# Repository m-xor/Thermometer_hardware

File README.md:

# Thermometer_hardware

PCBs designed for ZS60 universal case https://www.tme.eu/pl/details/z60-abs/obudowy-z-panelem/kradex/z60-abs/
The device consists of three PCB:
- LCD display board

- main board

- receiver board

- The device

Firmware: https://github.com/m-xor/Thermometer_receiver

- Known issues
 * power socket is placed to deep
 * PA9, PA10 could be routed to solder pads in case of need accessing bootloader

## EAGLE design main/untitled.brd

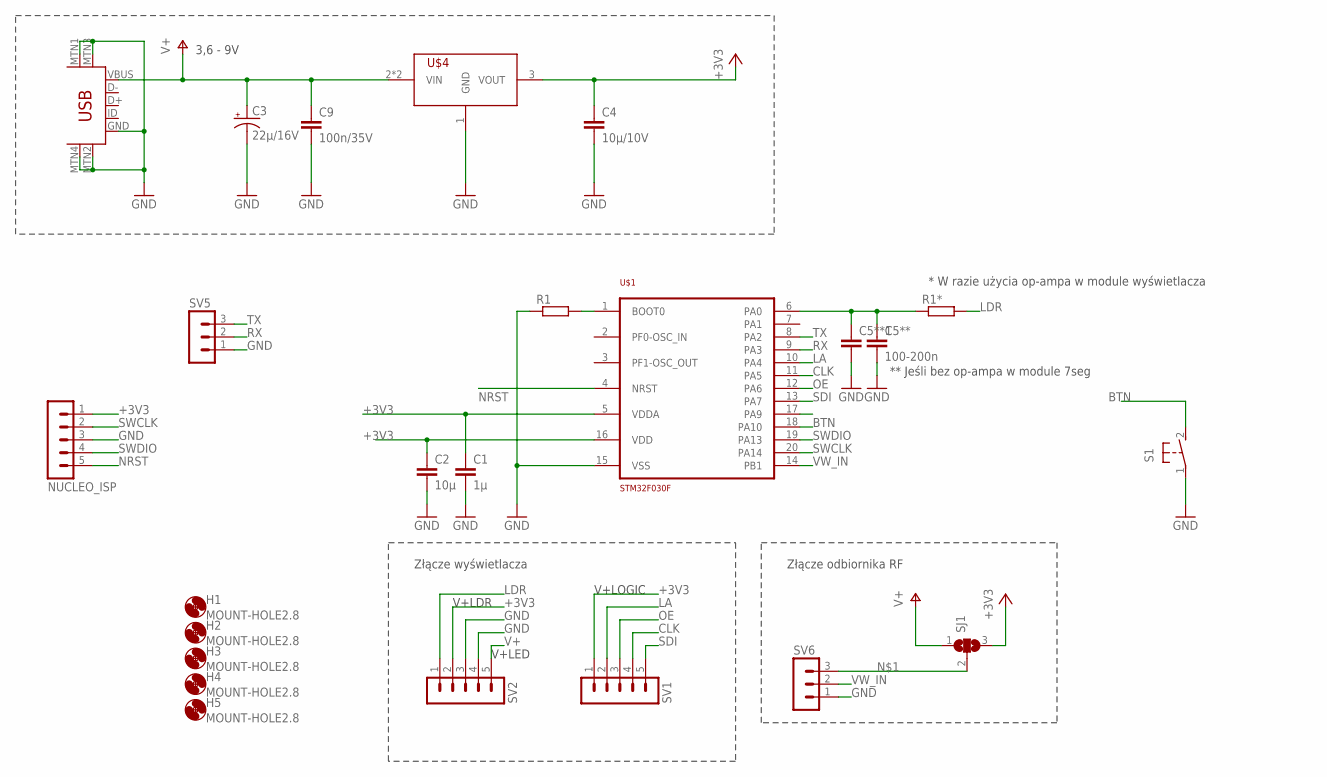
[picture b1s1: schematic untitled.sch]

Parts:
C1: 1µ; C0603
C2: 10µ; C0603
C3: 22µ/16V; E2,5-6
C4: 10µ/10V; C0603
C5**: 100-200n; C0603
C5**1: C-EUC0603; C0603
C9: 100n/35V; C0805
H1, H2, H3, H4, H5: MOUNT-HOLE2.8; 2,8
NUCLEO_ISP: MA05-1
R1, R1*: R-EU_R0603; R0603
S1: 31-XX; B3F-31XX
SJ1: SJ2W; SJ_2
SV1, SV2: MA05-1
SV5, SV6: MA03-1
U$1: STM32F030F; TSSOP20
U$2: USB-MINIB-5PIN; USB-MINIB
U$4: HT7333; SOT89

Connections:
+3V3: C1.1, C2.1, C4.1, NUCLEO_ISP.1, SJ1.3, SV1.1, SV2.2, U$1.5 (VDDA), U$1.16 (VDD), U$4.3 (VOUT)
BTN: S1.2 (S), U$1.18 (PA10)
CLK: SV1.4, U$1.11 (PA5)
GND: C1.2, C2.2, C3.-, C4.2, C5**.2, C5**1.2, C9.2, NUCLEO_ISP.3, R1.1, S1.1, SV2.3, SV2.4, SV5.1, SV6.1, U$1.15 (VSS), U$2.GND, U$2.MTN1 (MTN2), U$2.MTN2 (MTN3), U$2.MTN3 (MTN1), U$2.MTN4, U$4.1 (GND)
LA: SV1.2, U$1.10 (PA4)
LDR: R1*.2, SV2.1
unnamed: SJ1.2, SV6.3
unnamed: C5**.1, C5**1.1, R1*.1, U$1.6 (PA0)
unnamed: R1.2, U$1.1 (BOOT0)
NRST: NUCLEO_ISP.5, U$1.4 (NRST)
OE: SV1.3, U$1.12 (PA6)
RX: SV5.2, U$1.9 (PA3)
SDI: SV1.5, U$1.13 (PA7)
SWCLK: NUCLEO_ISP.2, U$1.20 (PA14)
SWDIO: NUCLEO_ISP.4, U$1.19 (PA13)
TX: SV5.3, U$1.8 (PA2)
V+: C3.+, C9.1, SJ1.1, SV2.5, U$2.VBUS, U$4.2 (VIN), U$4.2.1 (VIN)
VW_IN: SV6.2, U$1.14 (PB1)

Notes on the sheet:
* W razie użycia op-ampa w module wyświetlacza
** Jeśli bez op-ampa w module 7seg
3,6 - 9V
Złącze wyświetlacza
Złącze odbiornika RF
V+LDR
V+LED
V+LOGIC

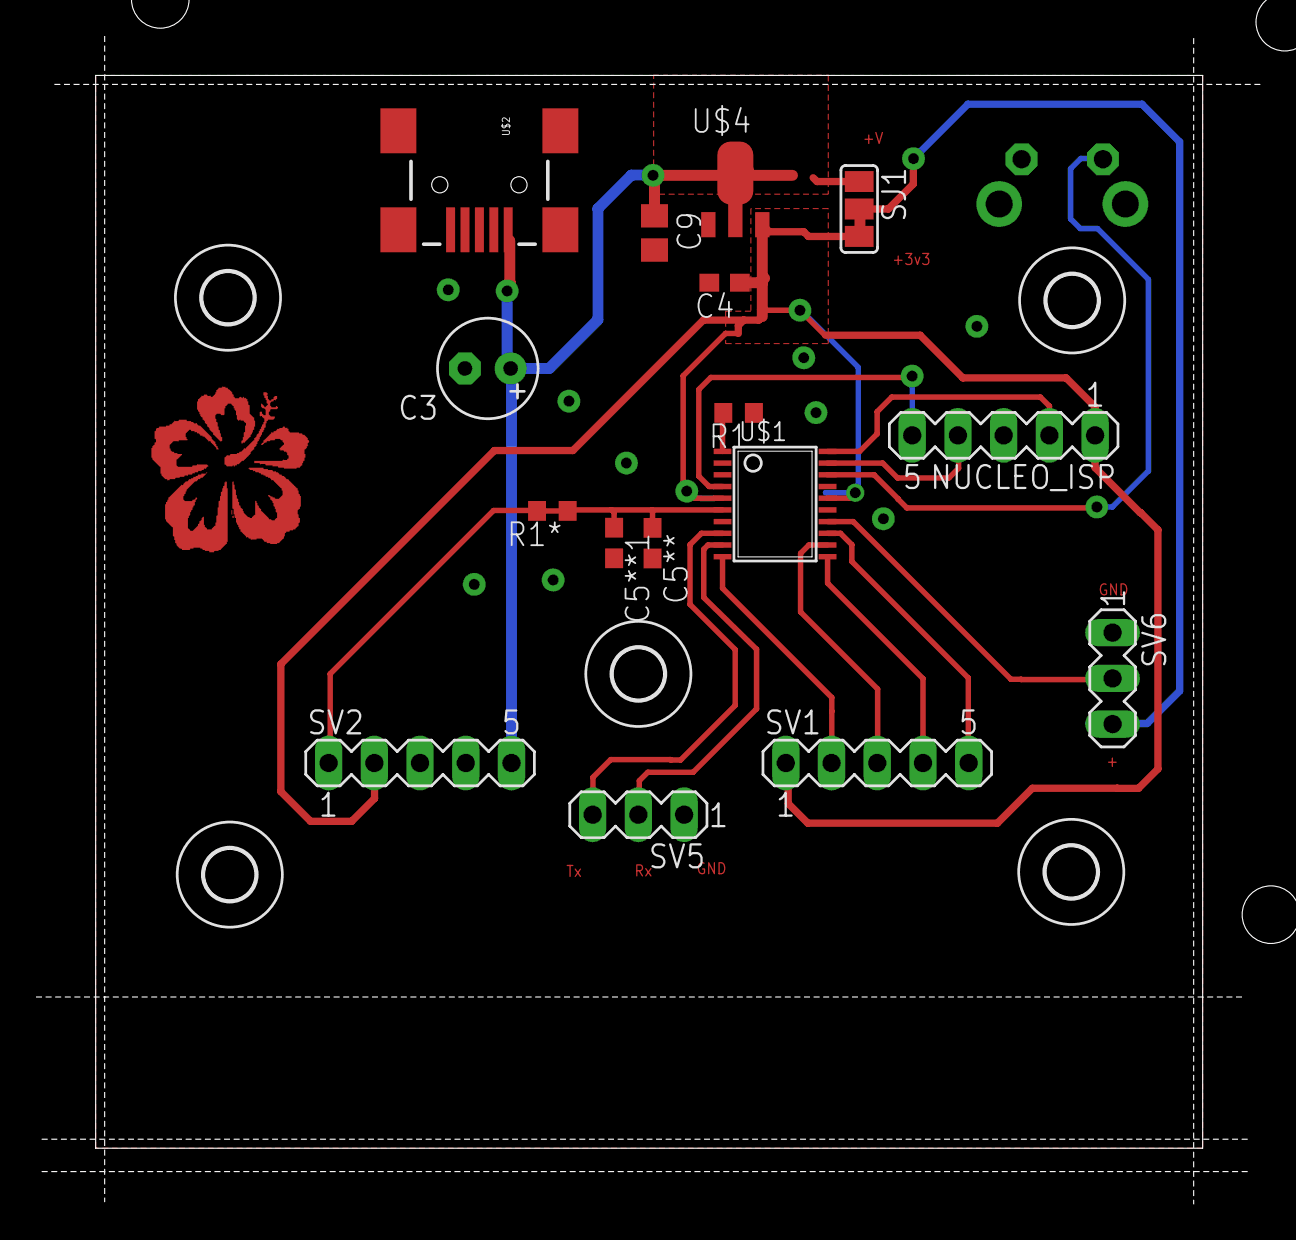
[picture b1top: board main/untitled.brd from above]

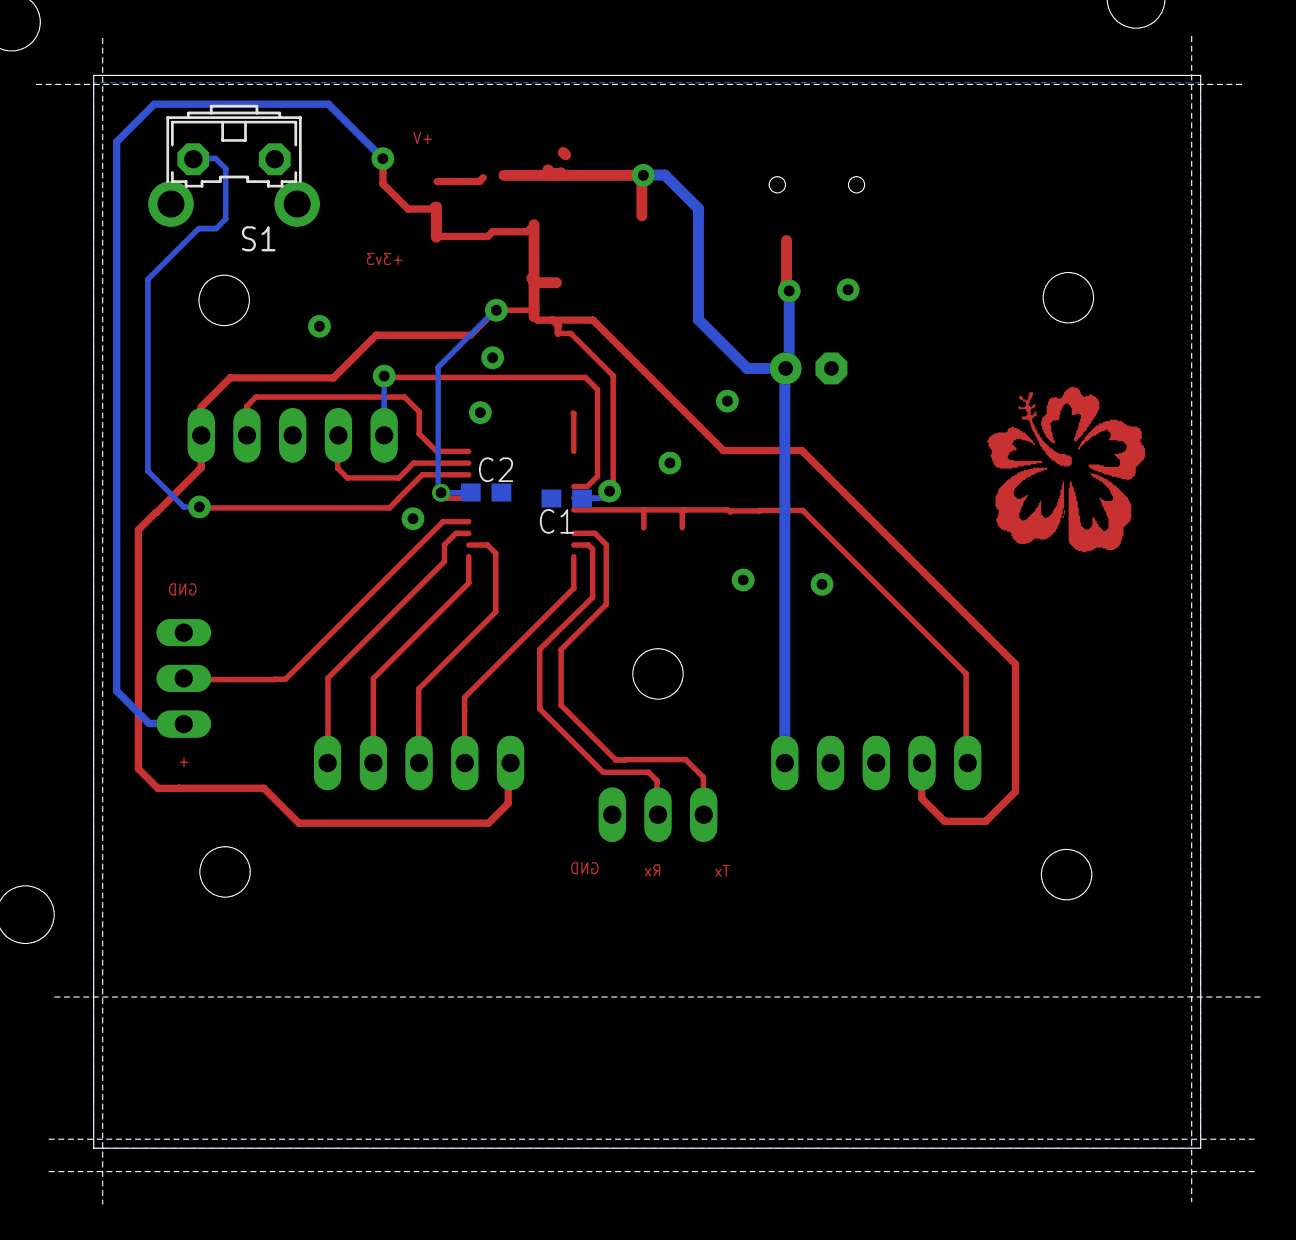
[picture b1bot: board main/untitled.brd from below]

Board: 2 copper layers, 61.5 x 59.6 mm, 26 parts (4 on the bottom side), 18 nets.

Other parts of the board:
DRILEGEND: DRILEGEND
U$3: LOGO_SMALL

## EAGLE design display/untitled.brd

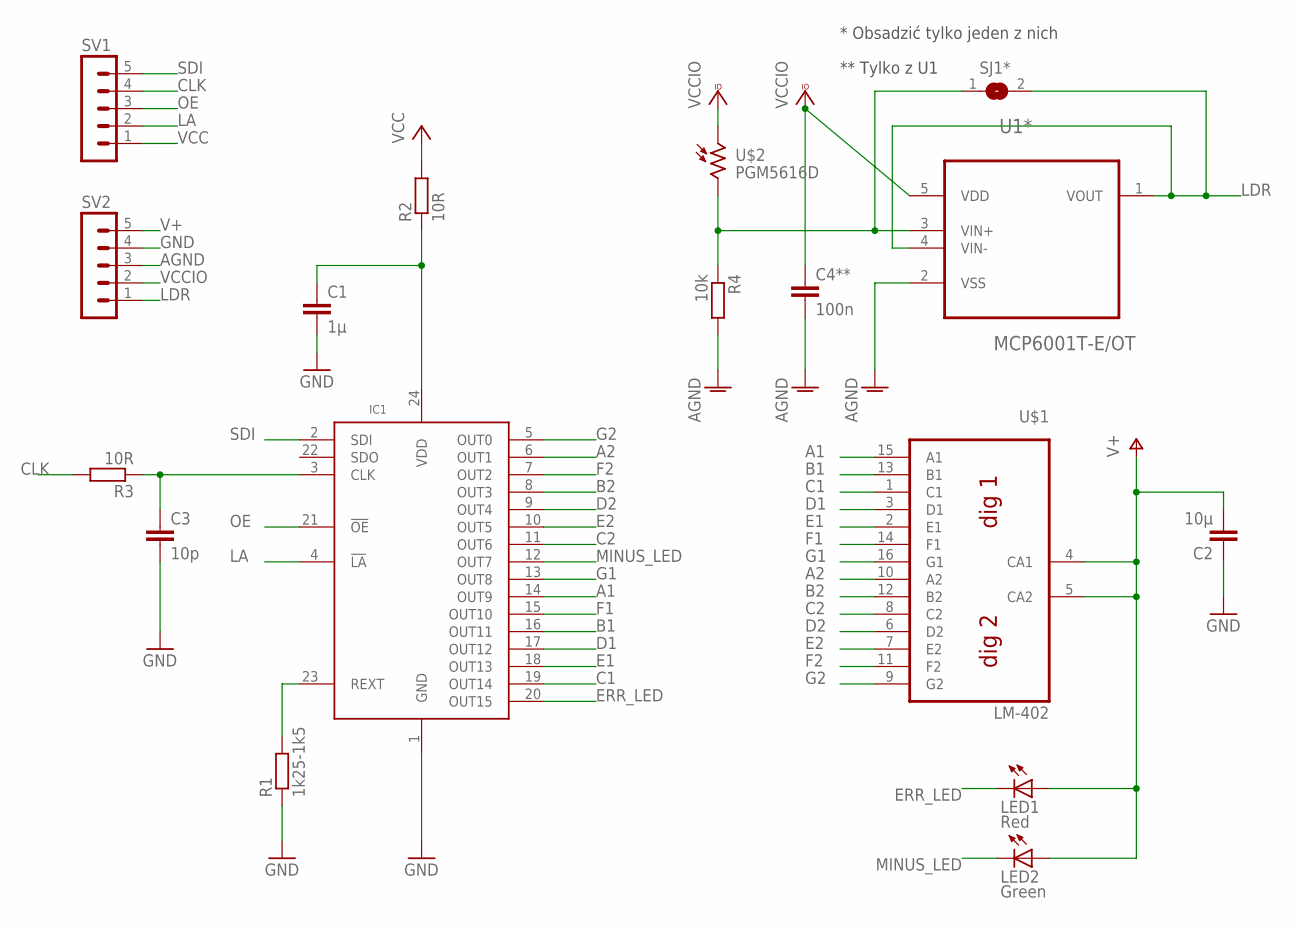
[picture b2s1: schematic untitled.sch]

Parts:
C1: 1µ; C0603K
C2: 10µ; C0603K
C3: 10p; C050-030X075
C4**: 100n; C0603K
IC1: SCT24; SSOP24
LED1: Red; LED3MM
LED2: Green; LED3MM
R1: 1k25-1k5; M0805
R2: 10R; R0805
R3: 10R; M0805
R4: 10k; M0805
SJ1*: SJ
SV1, SV2: MA05-1
U1*: MCP6001T-E/OT; SOT95P270X145-5N
U$1: LB-402
U$2: PGM5616D; PHOTO_5_34

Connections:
A1: IC1.14 (OUT9), U$1.15 (A1)
A2: IC1.6 (OUT1), U$1.10 (A2)
AGND: C4**.2, R4.2, SV2.3, U1*.2 (VSS)
B1: IC1.16 (OUT11), U$1.13 (B1)
B2: IC1.8 (OUT3), U$1.12 (B2)
C1: IC1.19 (OUT14), U$1.1 (C1)
C2: IC1.11 (OUT6), U$1.8 (C2)
CLK: R3.2, SV1.4
D1: IC1.17 (OUT12), U$1.3 (D1)
D2: IC1.9 (OUT4), U$1.6 (D2)
E1: IC1.18 (OUT13), U$1.2 (E1)
E2: IC1.10 (OUT5), U$1.7 (E2)
ERR_LED: IC1.20 (OUT15), LED1.K (C)
F1: IC1.15 (OUT10), U$1.14 (F1)
F2: IC1.7 (OUT2), U$1.11 (F2)
G1: IC1.13 (OUT8), U$1.16 (G1)
G2: IC1.5 (OUT0), U$1.9 (G2)
GND: C1.2, C2.1, C3.2, IC1.1 (GND), R1.1, SV2.4
LA: IC1.4 (!LA), SV1.2
LDR: SJ1*.2, SV2.1, U1*.1 (VOUT), U1*.4 (VIN-)
MINUS_LED: IC1.12 (OUT7), LED2.K (C)
unnamed: C1.1, IC1.24 (VDD), R2.1
unnamed: IC1.23 (REXT), R1.2
unnamed: C3.1, IC1.3 (CLK), R3.1
unnamed: R4.1, SJ1*.1, U1*.3 (VIN+), U$2.2
OE: IC1.21 (!OE), SV1.3
SDI: IC1.2 (SDI), SV1.5
V+: C2.2, LED1.A, LED2.A, SV2.5, U$1.4 (CA1), U$1.5 (CA2)
VCC: R2.2, SV1.1
VCCIO: C4**.1, SV2.2, U1*.5 (VDD), U$2.1

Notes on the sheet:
* Obsadzić tylko jeden z nich
** Tylko z U1

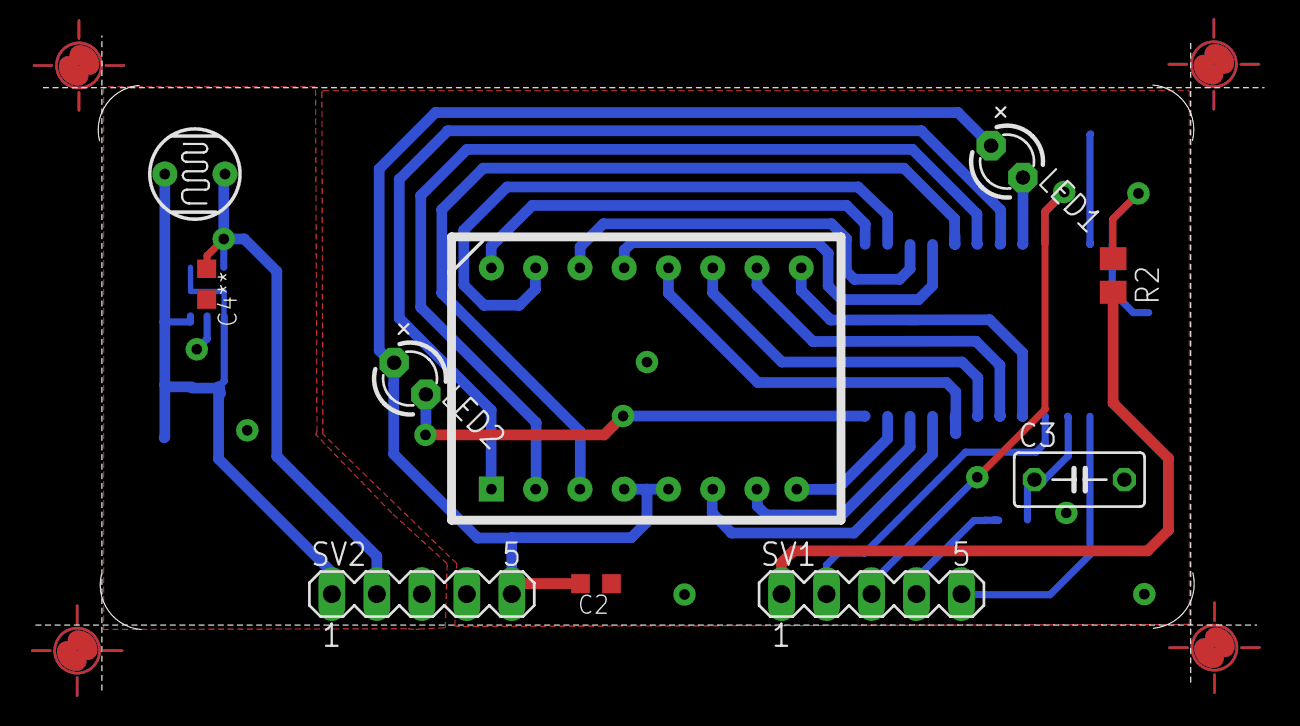
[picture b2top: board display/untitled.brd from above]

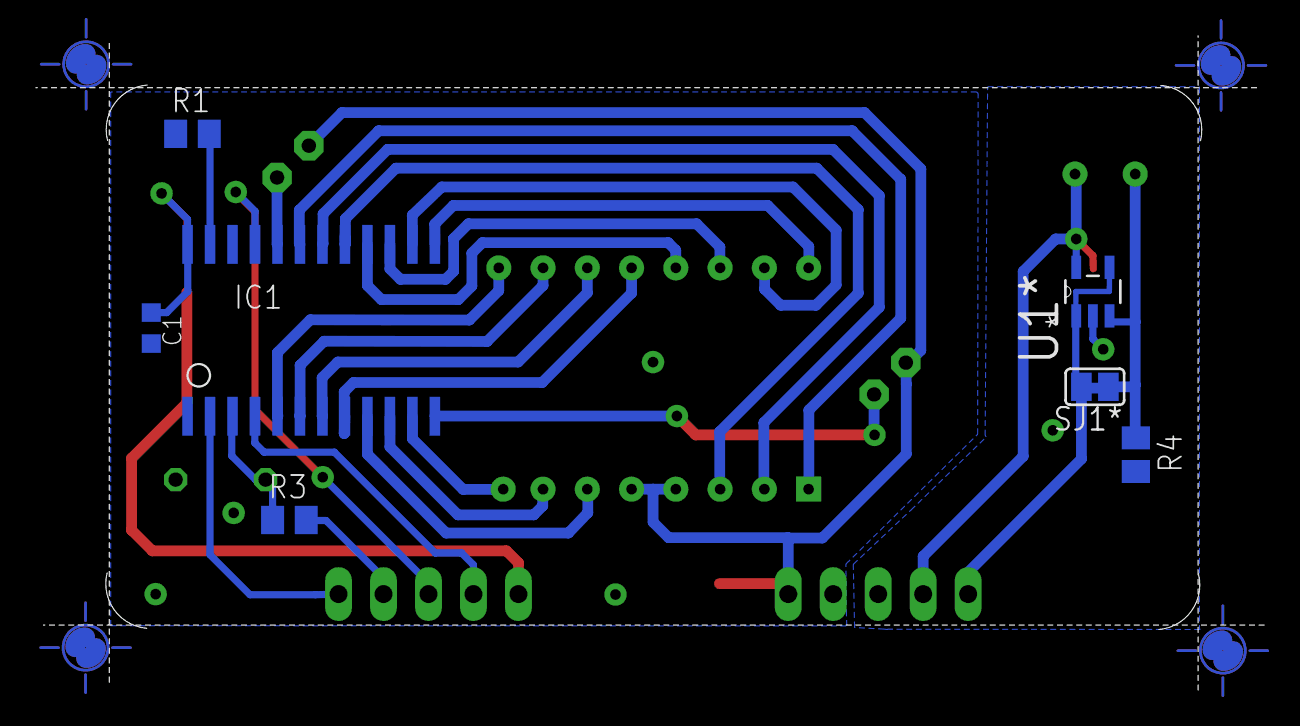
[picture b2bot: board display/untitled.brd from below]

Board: 2 copper layers, 69.4 x 37.0 mm, 22 parts (7 on the bottom side), 30 nets.

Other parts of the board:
DRILEGEND: DRILEGEND
U$3, U$4, U$5, U$6: PASS-ROUND

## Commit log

2020-06-12 ultimate version
2020-06-12 Fabrication
2020-06-12 Fabrication cont.
2020-06-14 main board's assembly
2020-06-14 the end

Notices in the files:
parts and their libraries:
SparkFun: Licensing: CC v3.0 Share-Alike You are welcome to use this library for commercial purposes.
